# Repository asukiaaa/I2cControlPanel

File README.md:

# I2cControlPanel

A wired control panel.

# Where to buy

- [I2cControlPanel | スイッチサイエンス](https://www.switch-science.com/catalog/6824/)

# Components

- [ATmega328PB-MU](https://www.digikey.jp/product-detail/ja/microchip-technology/ATMEGA328PB-MUR/ATMEGA328PB-MURCT-ND/5722708)
- [PS4 joy stick](https://ja.aliexpress.com/item/1005001729380060.html)
- [PS4 joy stick cap](https://ja.aliexpress.com/item/32964247181.html)
- [THT encoder](https://ja.aliexpress.com/item/1005001556801559.html)
- [Switch 12mm black](https://akizukidenshi.com/catalog/g/gP-09826/)
- [LCD 8x2](https://akizukidenshi.com/catalog/g/gP-06669/)
- [Slide switch](https://akizukidenshi.com/catalog/g/gP-12723/)
- [3V3 regulator](https://akizukidenshi.com/catalog/g/gI-10675/)
- [LED 0603 green](https://akizukidenshi.com/catalog/g/gI-06417/)
- [0.47uf 0402](https://akizukidenshi.com/catalog/g/gP-07504/)
- [0.01uf 0603](https://akizukidenshi.com/catalog/g/gP-13387/)
- 0.1uf 0603
- [Diode array](https://www.digikey.jp/product-detail/ja/toshiba-semiconductor-and-storage/1SS309-TE85L-F/1SS309-TE85LF-CT-ND/4304019)
- 10k 0603

# Old components

- [Panel mount encoder](https://ja.aliexpress.com/item/32783863247.html)
- [Low height joystick](https://ja.aliexpress.com/item/4000540937190.html)
- [Low height joystick cap](https://ja.aliexpress.com/item/33035062962.html)
- [Diode](https://akizukidenshi.com/catalog/g/gI-06467/)

# License

MIT

# References

- [エンコーダー（可変抵抗）が付いた有線コントローラーを作ってみた](https://asukiaaa.blogspot.com/2020/11/i2c-control-panel.html)
- [WiredController](https://github.com/asukiaaa/WiredControllerPcb)

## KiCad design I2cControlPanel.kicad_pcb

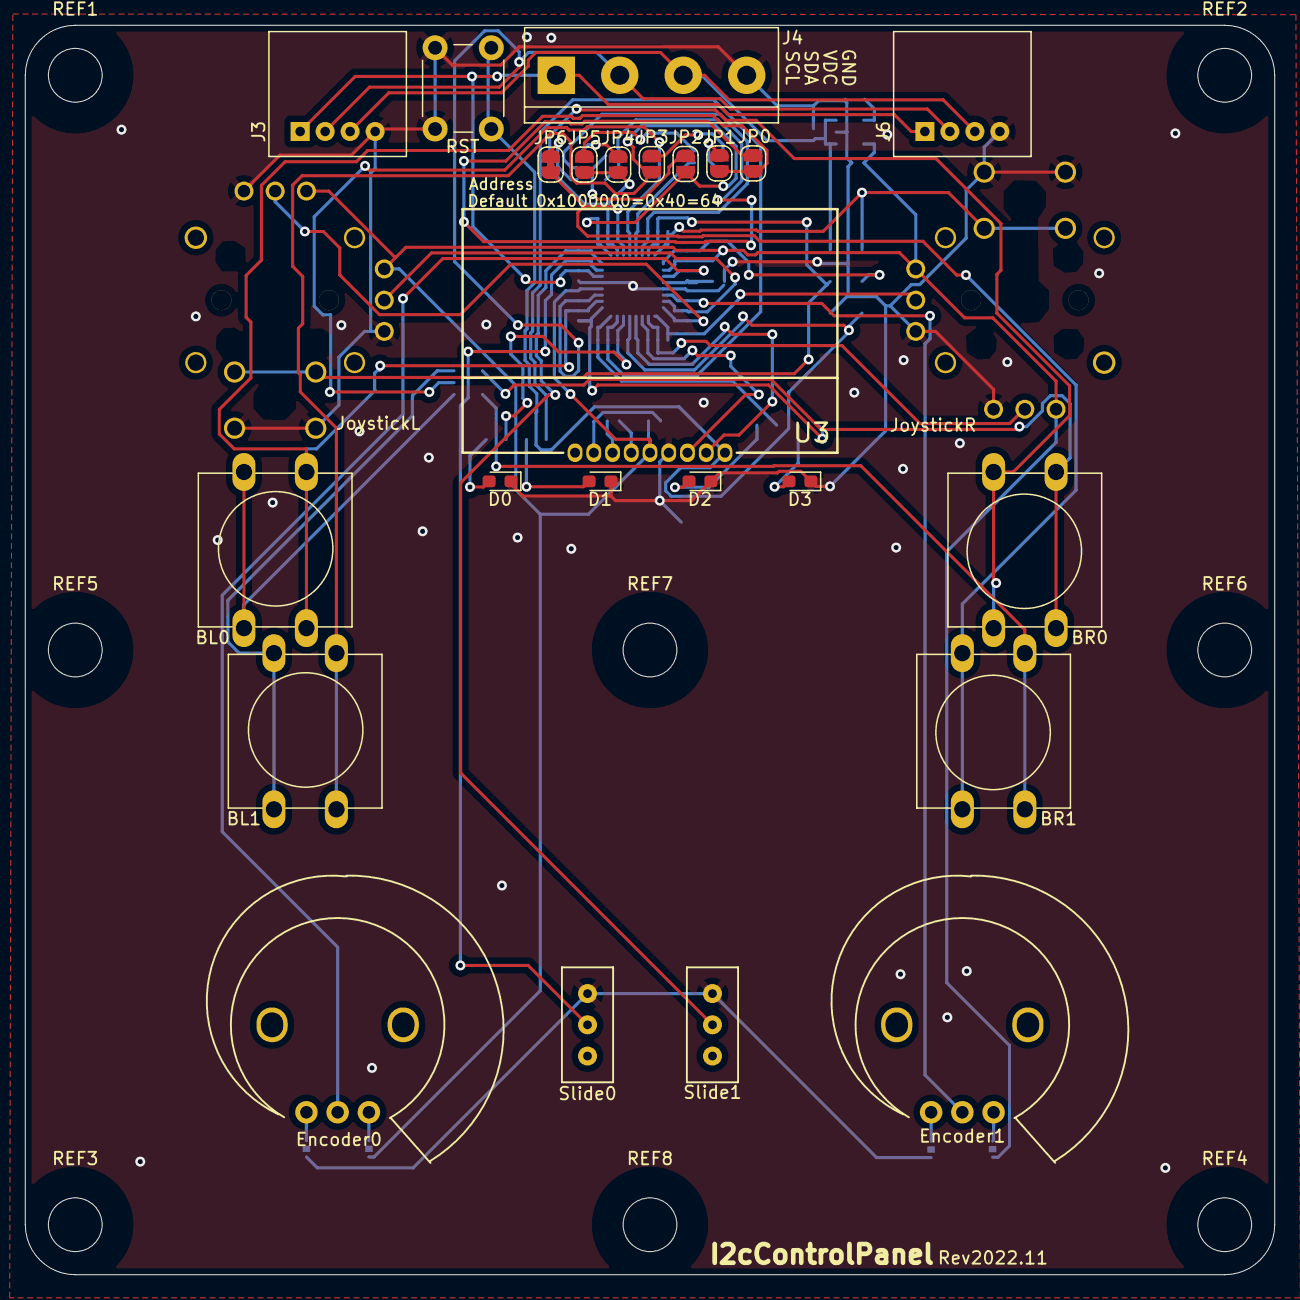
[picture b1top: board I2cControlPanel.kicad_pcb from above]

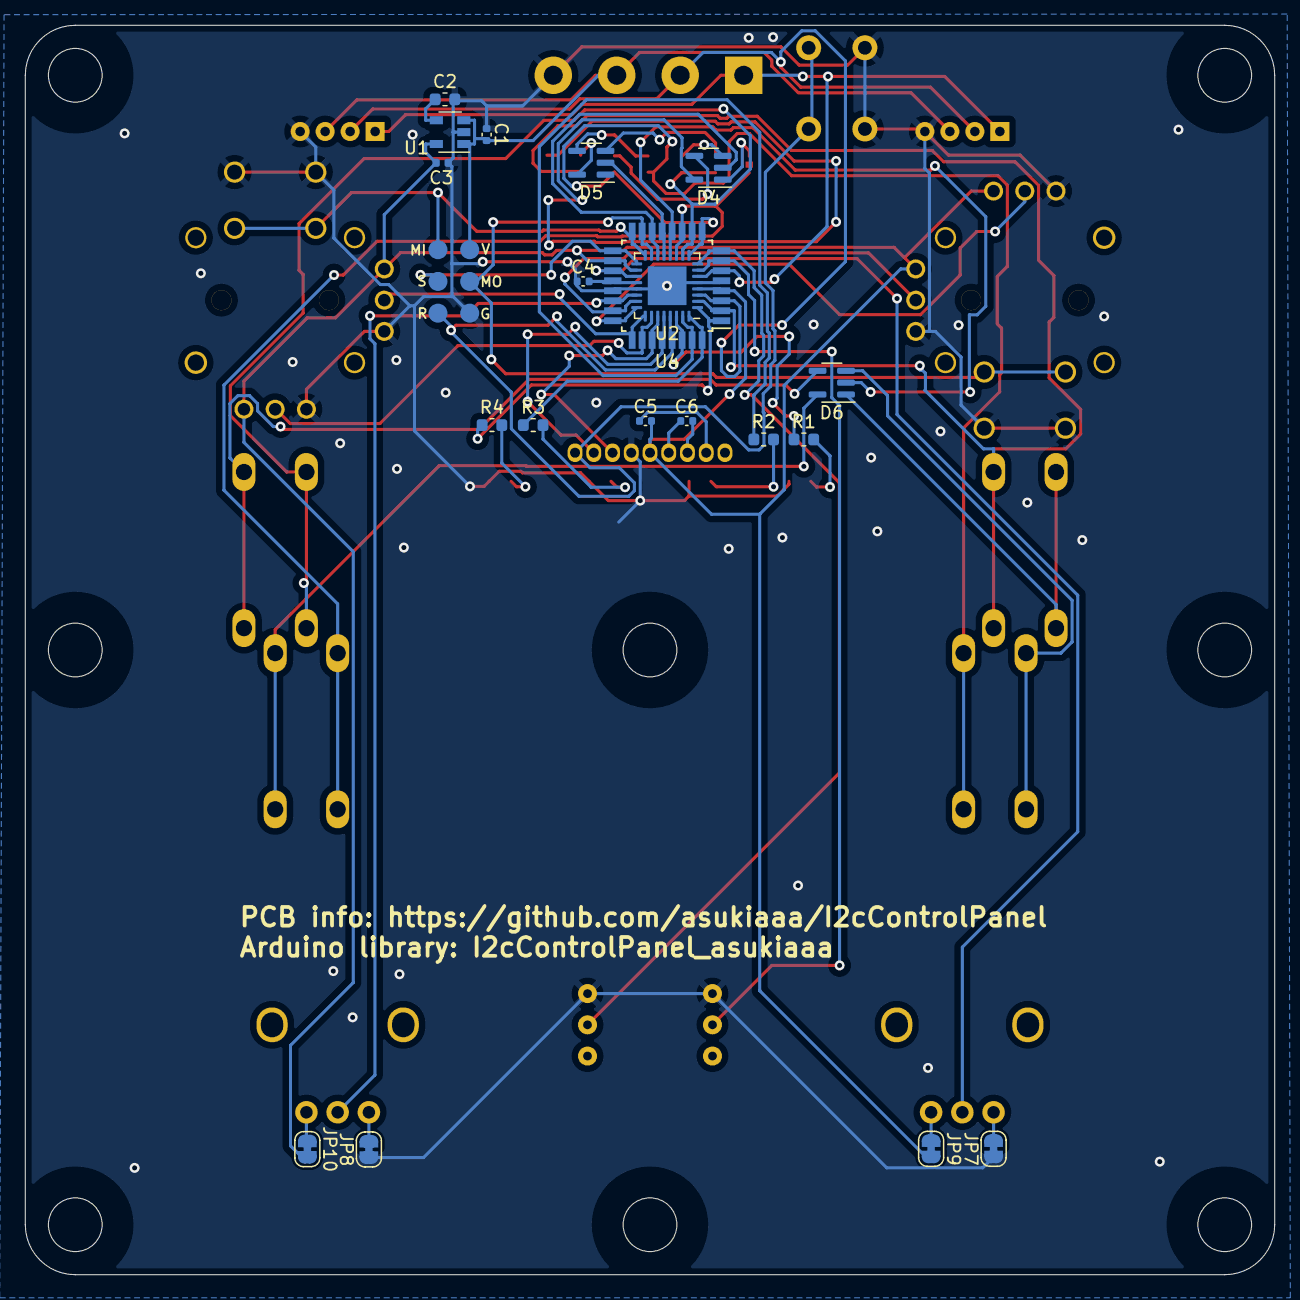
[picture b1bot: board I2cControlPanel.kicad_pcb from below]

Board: 2 copper layers, 100.0 x 100.0 mm, 55 parts (21 on the bottom side), 54 nets.

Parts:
BL0, BL1: SW_Push; SW_Center_PUSH-12mm
BR0, BR1: SW_Push; SW_Center_PUSH-12mm
C1, C4, C5, C6: 0.1u; C_0402_1005Metric
C2: 10n; C_0603_1608Metric
C3: 0.47u; C_0402_1005Metric
D0: LED0; D_0603_1608Metric_Pad1.05x0.95mm_HandSolder
D1: LED1; D_0603_1608Metric_Pad1.05x0.95mm_HandSolder
D2: LED2; D_0603_1608Metric_Pad1.05x0.95mm_HandSolder
D3: LED3; D_0603_1608Metric_Pad1.05x0.95mm_HandSolder
D4, D5, D6: 1SS309; SC-74-5_1.6x2.9mm_P0.95mm
Encoder0, Encoder1: R_POT_US; RoteryEncoderWithPowerLabel
J1: JoystickL; PS4tJoystick
J2: Conn_01x06; 2x03_P2.54mm_Pads
J3, J6: Conn_01x04; NS-Tech_Grove_1x04_P2mm_Horizontal
J4: Conn_01x04; TerminalBlock_bornier-4_P5.08mm
J5: JoystickR; PS4tJoystick
JP0, JP1, JP2, JP3, JP4, JP5: NO; SolderJumper-2_P1.3mm_Open_RoundedPad1.0x1.5mm
JP6, JP7, JP8, JP9, JP10: NC; SolderJumper-2_P1.3mm_Bridged_RoundedPad1.0x1.5mm
R1, R2, R3, R4: 10k; R_0603_1608Metric
REF1, REF2, REF3, REF4, REF5, REF6, REF7, REF8: MountingHole_4.3mm_M4_bare
SW6: SW_Push; SW_PUSH_6mm
Slide0, Slide1: SlideSwitch; SlideSwitch_SS12D01G4_2posi_1line
U1: NJM12888F33; SOT-23-5
U2: ATmega328PB-MU; QFN-32-1EP_5x5mm_P0.5mm_EP3.1x3.1mm
U3: AQM0802; AQM0802A-RN-GBW
U4: ATmega328PB-A; TQFP-32_7x7mm_P0.8mm_short_inner

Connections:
+3V3: C3.1, C5.2, J1.3, J1.4, J5.1, J5.6, JP9.2, JP10.2, U1.5 (Vout), U2.4 (VCC), U2.18 (AVCC), U3.5 (VDD), U4.4 (VCC), U4.18 (AVCC)
/BTN0: BL0.2, JP0.1, JP1.1, U2.2 (PD4), U4.2 (PD4)
/BTN1: BL1.2, JP2.1, JP3.1, U2.9 (PD5), U4.9 (PD5)
/BTN2: BR0.2, JP4.1, JP5.1, U2.10 (PD6), U4.10 (PD6)
/BTN3: BR1.2, JP6.1, U2.11 (PD7), U4.11 (PD7)
/BtnSig0: D6.2, U2.12 (PB0), U4.12 (PB0)
/BtnSig1: D5.2, U2.13 (PB1), U4.13 (PB1)
/BtnSig2: D4.2, U2.14 (PB2), U4.14 (PB2)
/HoriValueL: J1.2, U2.24 (PC1), U4.24 (PC1)
/HoriValueR: J5.2, U2.26 (PC3), U4.26 (PC3)
/JoyBtnL: J1.7, J2.4, U2.15 (PB3), U4.15 (PB3)
/JoyBtnR: J2.1, J5.7, U2.16 (PB4), U4.16 (PB4)
/LED0: R1.1, U2.30 (PD0), U4.30 (PD0)
/LED1: R2.1, U2.31 (PD1), U4.31 (PD1)
/LED2: R3.1, U2.32 (PD2), U4.32 (PD2)
/LED3: R4.1, U2.1 (PD3), U4.1 (PD3)
/RST: J2.5, SW6.1, U2.29 (~RESET/PC6), U3.9 (XRSETB), U4.29 (~RESET/PC6)
/Rotery1: Encoder0.2, U2.19 (PE2), U4.19 (PE2)
/Rotery2: Encoder1.2, U2.22 (PE3), U4.22 (PE3)
/SCK: J2.3, U2.17 (PB5), U4.17 (PB5)
/SCL: J3.1, J4.1, J6.1, U2.6 (PE1), U4.6 (PE1)
/SCL_inside: U2.28 (PC5), U3.8 (SCL), U4.28 (PC5)
/SDA: J3.2, J4.2, J6.2, U2.3 (PE0), U4.3 (PE0)
/SDA_inside: U2.27 (PC4), U3.7 (SDA), U4.27 (PC4)
/Slide0: Slide0.2 (B), U2.7 (XTAL1/PB6), U4.7 (XTAL1/PB6)
/Slide1: Slide1.2 (B), U2.8 (XTAL2/PB7), U4.8 (XTAL2/PB7)
/VertValueL: J1.5, U2.23 (PC0), U4.23 (PC0)
/VertValueR: J5.5, U2.25 (PC2), U4.25 (PC2)
GND: C1.2, C2.2, C3.2, C4.1, D0.1 (K), D1.1 (K), D2.1 (K), D3.1 (K), J1.1, J1.6, J1.8, J2.6, J3.4, J4.4, J5.3, J5.4, J5.8, J6.4, JP7.1, JP8.1, SW6.2, Slide0.1 (A), Slide1.1 (A), U1.2 (GND), U2.5 (GND), U2.21 (GND), U2.33 (GND), U3.6 (VSS), U4.5 (GND), U4.21 (GND)
unnamed: BL0.1, D6.1
unnamed: BL1.1, D6.3
unnamed: BR0.1, D6.4
unnamed: BR1.1, D6.5
unnamed: C2.1, U1.4 (CS)
unnamed: C4.2, U2.20 (AREF), U4.20 (AREF)
unnamed: C5.1, U3.2 (VOUT)
unnamed: C6.1, U3.4 (CAP1P)
unnamed: C6.2, U3.3 (CAP1N)
unnamed: D0.2 (A), R1.2
unnamed: D1.2 (A), R2.2
unnamed: D2.2 (A), R3.2
unnamed: D3.2 (A), R4.2
unnamed: D4.1, JP6.2
unnamed: D4.3, JP4.2
unnamed: D4.4, JP2.2
unnamed: D4.5, JP0.2
unnamed: D5.3, JP5.2
unnamed: D5.4, JP3.2
unnamed: D5.5, JP1.2
unnamed: Encoder0.1, JP7.2
unnamed: Encoder0.3, JP9.1
unnamed: Encoder1.1, JP8.2
unnamed: Encoder1.3, JP10.1
VDC: C1.1, J2.2, J3.3, J4.3, J6.3, U1.1 (VIN), U1.3 (CTL)

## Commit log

2020-08-14 Replace gnd and 3v3 for right joy stick
2020-08-23 Update footprint of volume
2020-08-29 Correct button line for address pads
2020-09-03 Update slide switch position and labels for each buttons
2020-09-03 Update revision to 2020.08 and github url and arduino library info
2020-09-19 Change pin assign for left joy hori and vert
2020-09-19 Update list of components on readme
2020-09-20 Update hole position of volume
2020-09-24 Remove R7 resistor
2020-09-26 Replace vert and hori for joy
2020-09-26 Change pad for diode
2020-09-26 Update pad of led for soldering by hand
2020-09-26 Change slide switch
2020-11-29 Add size info to pcb
2020-12-14 Remove redundant bom files
2020-12-14 Plot schematic as pdf
2020-12-14 Remove 1k register from component list of readme
2020-12-14 Add image to readme
2020-12-14 Add reference links to readme
2021-03-12 Add link of store url to readme
2021-03-12 Use diode array and add mounting holes as Rev2021.03
2021-04-06 Change joystick for ps4 type
2021-04-06 Assign 0402 condensor for 0.1uf
2021-04-25 Change position of c1 label
2021-04-29 Change rotery encoder and remove pull up for internal i2c
2021-10-01 Create bom.csv and update components on readme
2022-06-27 Update for KiCad6
2022-06-27 Assign asukiaaa-kicad- symbols and footprints
2022-06-27 Change mounting hole as bare
2022-07-27 Joint missing BtnSig1 line on pcb
2022-11-09 Add A package for ATmega328PB
2022-11-09 Add bom for a package for atmega328pb
2022-12-21 Add bottom space as rev2023.01
2023-03-19 Use photo of rev2023.01 on top
2023-03-19 Add a link for arduino library
2023-06-26 Add frame_2x2
